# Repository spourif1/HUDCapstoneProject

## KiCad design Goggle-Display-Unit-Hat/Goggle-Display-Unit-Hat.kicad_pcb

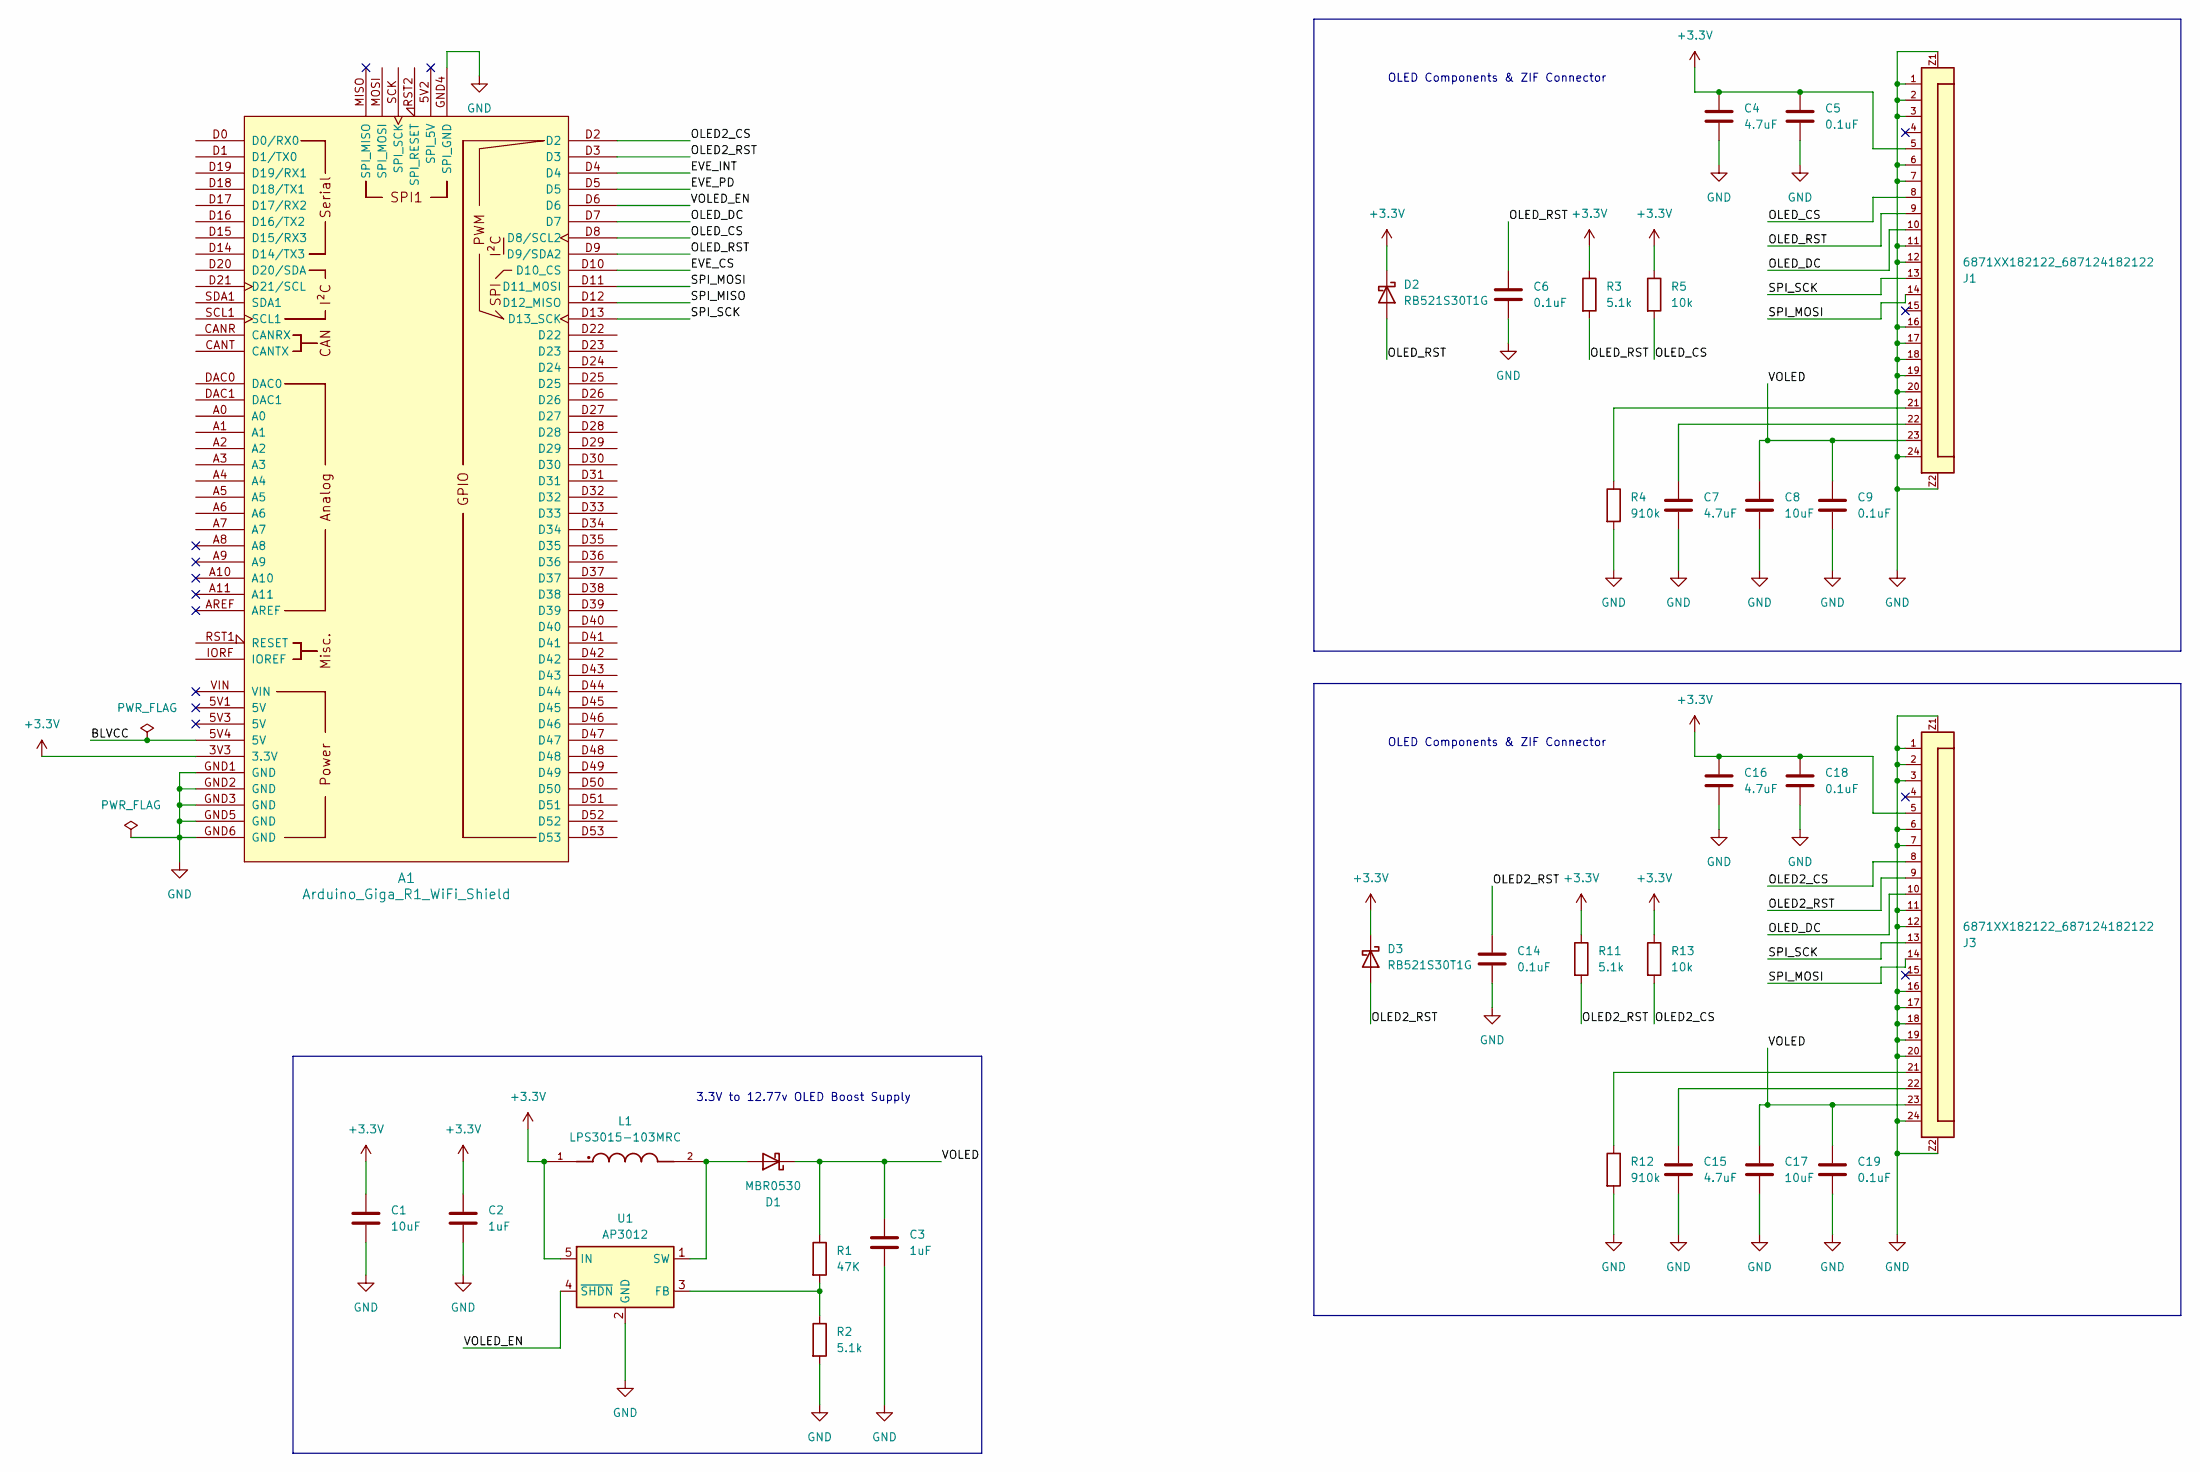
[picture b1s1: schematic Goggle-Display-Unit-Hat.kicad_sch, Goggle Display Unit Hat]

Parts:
A1: Arduino_Giga_R1_WiFi_Shield
C1, C8, C17: 10uF; C_1206_3216Metric_Pad1.33x1.80mm_HandSolder
C2, C3: 1uF; C_0603_1608Metric_Pad1.08x0.95mm_HandSolder
C4, C7, C15, C16: 4.7uF; C_0603_1608Metric_Pad1.08x0.95mm_HandSolder
C5, C6, C9, C14, C18, C19: 0.1uF; C_0603_1608Metric_Pad1.08x0.95mm_HandSolder
D1: MBR0530; D_SOD-123
D2, D3: RB521S30T1G; D_SOD-523
J1, J3: 6871XX182122_687124182122; 687124182122
L1: LPS3015-103MRC; IND_LPS3015-103MRC; PARTREV 12/13/21
R1: 47K; R_0603_1608Metric_Pad0.98x0.95mm_HandSolder
R2, R3, R11: 5.1k; R_0603_1608Metric_Pad0.98x0.95mm_HandSolder
R4, R12: 910k; R_0603_1608Metric_Pad0.98x0.95mm_HandSolder
R5, R13: 10k; R_0603_1608Metric_Pad0.98x0.95mm_HandSolder
U1: AP3012; SOT-23-5

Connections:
+3.3V: A1.3V3 (3.3V), C1.1, C2.1, C4.1, C5.1, C16.1, C18.1, D2.1 (K), D3.1 (K), J1.5, J3.5, L1.1, R3.1, R5.1, R11.1, R13.1, U1.5 (IN)
/BLVCC: A1.5V4 (5V)
/EVE_CS: A1.D10 (D10_CS)
/EVE_INT: A1.D4
/EVE_PD: A1.D5
/OLED2_CS: A1.D2, J3.8, R13.2
/OLED2_RST: A1.D3, C14.1, D3.2 (A), J3.9, R11.2
/OLED_CS: A1.D8 (D8/SCL2), J1.8, R5.2
/OLED_DC: A1.D7, J1.10, J3.10
/OLED_RST: A1.D9 (D9/SDA2), C6.1, D2.2 (A), J1.9, R3.2
/SPI_MISO: A1.D12 (D12_MISO)
/SPI_MOSI: A1.D11 (D11_MOSI), J1.14, J3.14
/SPI_SCK: A1.D13 (D13_SCK), J1.13, J3.13
/VOLED: C3.1, C8.1, C9.1, C17.1, C19.1, D1.1 (K), J1.23, J3.23, R1.1
/VOLED_EN: A1.D6, U1.4 (~SHDN)
GND: A1.GND1 (GND), A1.GND2 (GND), A1.GND3 (GND), A1.GND4 (SPI_GND), A1.GND5 (GND), A1.GND6 (GND), C1.2, C2.2, C3.2, C4.2, C5.2, C6.2, C7.2, C8.2, C9.2, C14.2, C15.2, C16.2, C17.2, C18.2, C19.2, J1.1, J1.2, J1.3, J1.6, J1.7, J1.11, J1.12, J1.16, J1.17, J1.18, J1.19, J1.20, J1.24, J1.Z1, J1.Z2, J3.1, J3.2, J3.3, J3.6, J3.7, J3.11, J3.12, J3.16, J3.17, J3.18, J3.19, J3.20, J3.24, J3.Z1, J3.Z2, R2.2, R4.2, R12.2, U1.2 (GND)
unnamed: C7.1, J1.22
unnamed: C15.1, J3.22
unnamed: D1.2 (A), L1.2, U1.1 (SW)
unnamed: J1.21, R4.1
unnamed: J3.21, R12.1
unnamed: R1.2, R2.1, U1.3 (FB)

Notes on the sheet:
OLED Components & ZIF Connector
3.3V to 12.77v OLED Boost Supply

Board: 2 copper layers, 31 parts (0 on the bottom side), 17 nets, no tracks yet.
